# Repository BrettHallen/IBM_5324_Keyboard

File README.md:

# IBM System/23 Model 5324 Keyboard
Recreation of the keyboard for this computer to bring those without keyboards back to life.

## [Design References](/Design_Reference)

|     |Column A|Column B|Column C|Column D|Column E|Column F|Column G|Column H|Column I|Column J|Column K|
|-----|--------|--------|--------|--------|--------|--------|--------|--------|--------|--------|--------|
|Row 1| 6F/7F  | 3E     | 32     | 34     | 36     | 38     | 3A     | 3C     |        | 4B     |        |
|Row 2| 7C     | 31     | 33     | 35     | 37     |        | 39     | 3B     | 3D T   | 48     | 4C     |
|Row 3| 6D     | 20     | 22     | 24     | 26     |        | 28     | 2A     | 2C     | 47     | 49     |
|Row 4| 6C     | 54/74  | 21     | 23     | 25     | 27     | 29     | 2B     | 2D     | 44     | 4E     |
|Row 5| 6E     | 57/77  | 11     | 13     | 15     | 17     | 19     | 1B     | 59/79  | 45     | 46     |
|Row 6| 7D     | 70 T   | 12     | 14     | 16     |        | 18     | 1A     | 56/76  | 41     | 43     |
|Row 7| 71 T   | 73 T   | 0E     | 03     | 05     | 06     | 07     | 09     | 0B/7B  | 42     | 4D     |
|Row 8| 72 T   | 7E/5E  | 01     | 02     | 04     | 0F T   | 08     | 0A     | 68/78  | 40     | 4A     |

xx/yy = make/break key (send on release)<br>
T = typamatic key (repeat while held)<br>

## Keyboard Data Flow 
Refer p3-19 of the [SY34-0241-1 service manual.](/Datasheets/SY34-0241-1_IBM_5324_Computer_Service_Manual_May82_Keyboard.pdf)

The original keyboard uses a capacitive matrix where there is a capacitor for each key. When a key is pressed the capacitance increases.<br>

In my design we use standard key switches.<br>

The keyboard MCU has 11 drive lines to repeatedly scan the matrix - in my schematic these are the columns.<br>  

The increased capacitance of the active key's capacitor permits the drive-line (column) scan pulse to appear at one of the eight input lines to the sense amplifier - in my schematic these are the rows.<br>

The MCU uses the combination of the active drive line (column) and sense amplifier input line (row) to determine a scan code character (88 possible, 83 actually used).<br>

In my design the columns and rows are pulled high.  To scan the keyboard matrix we take each column low in turn.  A key press is detected when the key switch shorts the row to the column, taking the row low which is detected by the controller.  The combination of column and row is translated to a 5324 scan code and put on the bus via a buffer to ensure the 5324 accurately reads the code.<br>

An interrupt request (via DATA STROBE?) is sent to the Model 5324 processing unit which will then read the scan code character.<br>

## Key Caps
[Key cap layout](https://gist.github.com/0ddjob/6a0642893fc0fdca74740a1e6c51e858)

|Size |Count|
|-----|-----|
|1u   |68   |
|1.25u|2    |
|1.5u |2    |
|1.75u|2    |
|2u   |6    |
|2.25u|1    |
|3u   |1    |
|9.5u |1    |
|TOTAL|83   |

|Size|Key|
|-----|---|
|1.25u|Backslash|
|1.25u|Shift LH|
|1.5u|Shift RH|
|1.5u|Field Advance|
|1.75u|Backspace|
|1.75u|Shift Lock|
|2u|Field Exit|
|2u|NP +|
|2u|NP -|
|2u|NP 0|
|2u|NP .|
|2u|Alt|
|2u|Enter (vertical)|
|3u|Field + (vertical)|
|9.5u|Space|

## [KiCad Design](/KiCad)
[Schematic](/IBM_5324_Keyboard_Schematic.pdf)

## [N-Key Rollover (NKRO) Design](/KiCad_NKRO)
Adding diodes to each key switch on their row connection.  The original keyboard doesn't have these so the modified behaviour might not be expected, thus it's "experimental".

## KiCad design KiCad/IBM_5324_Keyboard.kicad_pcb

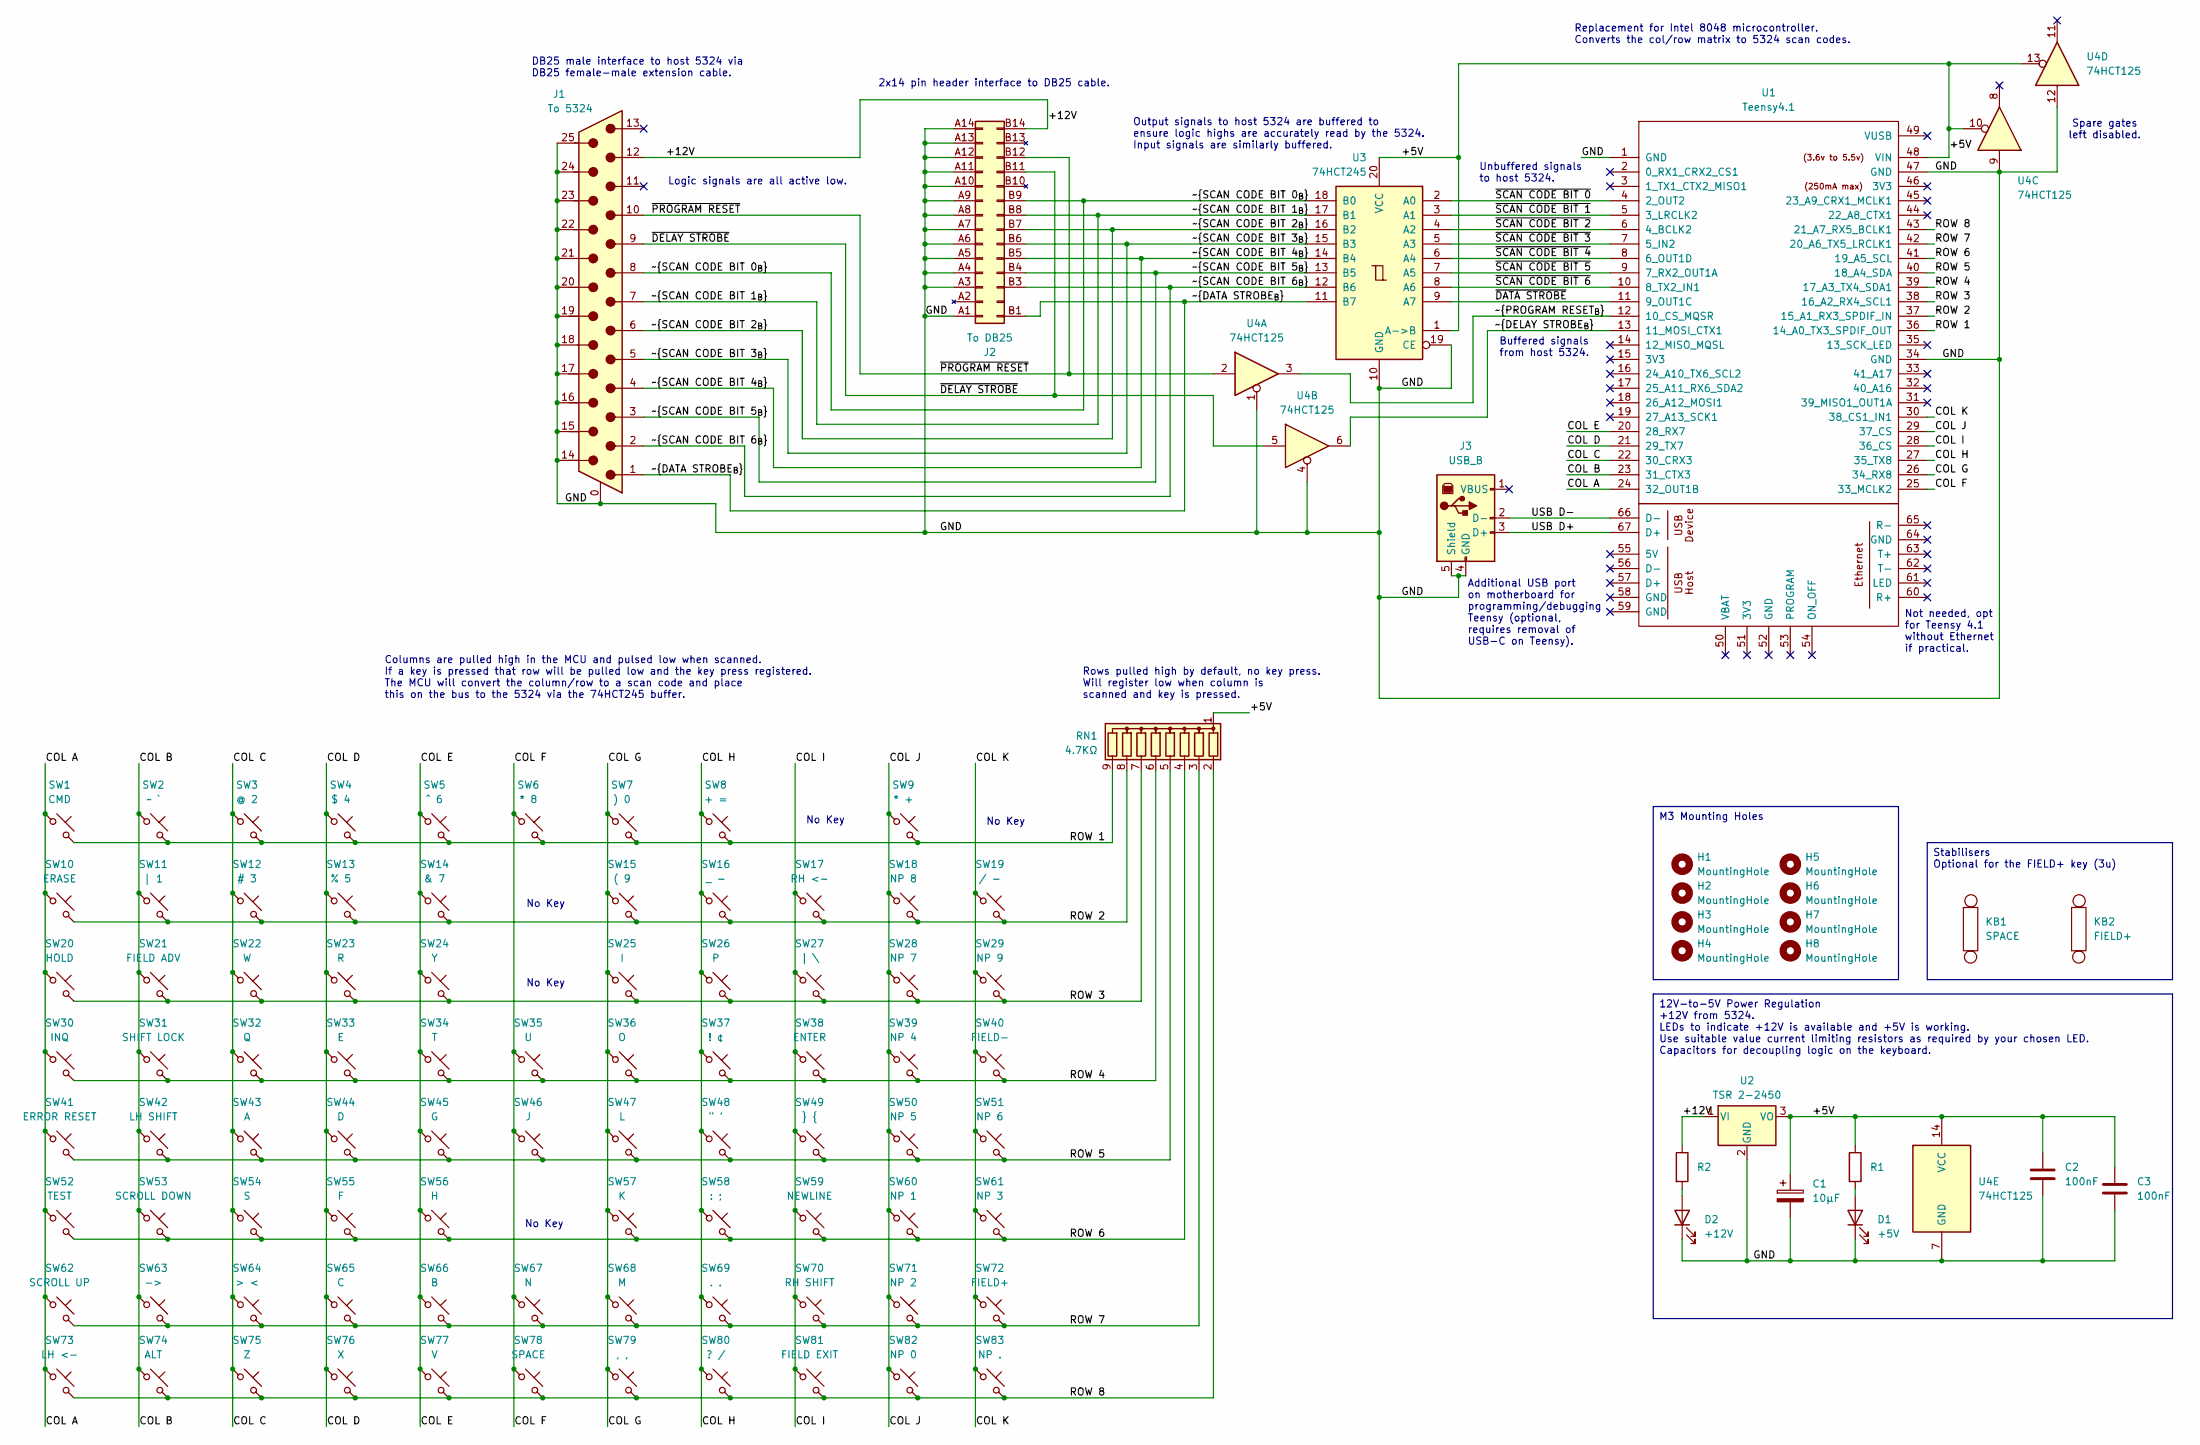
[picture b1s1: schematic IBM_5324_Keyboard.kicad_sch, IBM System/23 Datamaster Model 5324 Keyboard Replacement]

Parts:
C1: 10µF; CP_Radial_D5.0mm_P2.50mm
C2, C3: 100nF; C_Disc_D3.8mm_W2.6mm_P2.50mm
D1: +5V; LED_D5.0mm
D2: +12V; LED_D5.0mm
H1, H2, H3, H4, H5, H6, H7, H8: MountingHole; MountingHole_3.2mm_M3
J1: To 5324; L717SDB25P1ACH3R
J2: To DB25; PinHeader_2x14_P2.54mm_Vertical
J3: USB_B; USB_B_Lumberg_2411_02_Horizontal
KB1: SPACE; Stabilizer_Cherry_MX_8.00u
KB2: FIELD+; Stabilizer_Cherry_MX_3.00u
R1, R2: R; R_Axial_DIN0207_L6.3mm_D2.5mm_P7.62mm_Horizontal
RN1: 4.7KΩ; R_Array_SIP9
SW1: CMD; SW_Cherry_MX_PCB
SW2: ~ `; SW_Cherry_MX_PCB
SW3: @ 2; SW_Cherry_MX_PCB
SW4: $ 4; SW_Cherry_MX_PCB
SW5: ^ 6; SW_Cherry_MX_PCB
SW6: * 8; SW_Cherry_MX_PCB
SW7: ) 0; SW_Cherry_MX_PCB
SW8: + =; SW_Cherry_MX_PCB
SW9: * +; SW_Cherry_MX_PCB_1.75u
SW10: ERASE; SW_Cherry_MX_PCB
SW11: | 1; SW_Cherry_MX_PCB
SW12: # 3; SW_Cherry_MX_PCB
SW13: % 5; SW_Cherry_MX_PCB
SW14: & 7; SW_Cherry_MX_PCB
SW15: ( 9; SW_Cherry_MX_PCB
SW16: _ -; SW_Cherry_MX_PCB
SW17: RH <-; SW_Cherry_MX_PCB
SW18: NP 8; SW_Cherry_MX_PCB
SW19: / -; SW_Cherry_MX_PCB_1.75u
SW20: HOLD; SW_Cherry_MX_PCB
SW21: FIELD ADV; SW_Cherry_MX_PCB_1.50u
SW22: W; SW_Cherry_MX_PCB
SW23: R; SW_Cherry_MX_PCB
SW24: Y; SW_Cherry_MX_PCB
SW25: I; SW_Cherry_MX_PCB
SW26: P; SW_Cherry_MX_PCB
SW27: | \; SW_Cherry_MX_PCB
SW28: NP 7; SW_Cherry_MX_PCB
SW29: NP 9; SW_Cherry_MX_PCB
SW30: INQ; SW_Cherry_MX_PCB
SW31: SHIFT LOCK; SW_Cherry_MX_PCB_1.75u
SW32: Q; SW_Cherry_MX_PCB
SW33: E; SW_Cherry_MX_PCB
SW34: T; SW_Cherry_MX_PCB
SW35: U; SW_Cherry_MX_PCB
SW36: O; SW_Cherry_MX_PCB
SW37: ! ¢; SW_Cherry_MX_PCB
SW38: ENTER; SW_Cherry_MX_PCB_2.00u_90deg
SW39: NP 4; SW_Cherry_MX_PCB
SW40: FIELD-; SW_Cherry_MX_PCB
SW41: ERROR RESET; SW_Cherry_MX_PCB
SW42: LH SHIFT; SW_Cherry_MX_PCB_1.25u
SW43: A; SW_Cherry_MX_PCB
SW44: D; SW_Cherry_MX_PCB
SW45: G; SW_Cherry_MX_PCB
SW46: J; SW_Cherry_MX_PCB
SW47: L; SW_Cherry_MX_PCB
SW48: " '; SW_Cherry_MX_PCB
SW49: } {; SW_Cherry_MX_PCB
SW50: NP 5; SW_Cherry_MX_PCB
SW51: NP 6; SW_Cherry_MX_PCB
SW52: TEST; SW_Cherry_MX_PCB
SW53: SCROLL DOWN; SW_Cherry_MX_PCB
SW54: S; SW_Cherry_MX_PCB
SW55: F; SW_Cherry_MX_PCB
SW56: H; SW_Cherry_MX_PCB
SW57: K; SW_Cherry_MX_PCB
SW58: : ;; SW_Cherry_MX_PCB
SW59: NEWLINE; SW_Cherry_MX_PCB
SW60: NP 1; SW_Cherry_MX_PCB
SW61: NP 3; SW_Cherry_MX_PCB
SW62: SCROLL UP; SW_Cherry_MX_PCB
SW63: ->; SW_Cherry_MX_PCB
SW64: > <; SW_Cherry_MX_PCB_1.00u
SW65: C; SW_Cherry_MX_PCB
SW66: B; SW_Cherry_MX_PCB
SW67: N; SW_Cherry_MX_PCB
SW68: M; SW_Cherry_MX_PCB
SW69: . .; SW_Cherry_MX_PCB
SW70: RH SHIFT; SW_Cherry_MX_PCB_1.50u
SW71: NP 2; SW_Cherry_MX_PCB
SW72: FIELD+; SW_Cherry_MX_PCB_3.00u_90deg
SW73: LH <-; SW_Cherry_MX_PCB
SW74: ALT; SW_Cherry_MX_PCB_2.25u
SW75: Z; SW_Cherry_MX_PCB
SW76: X; SW_Cherry_MX_PCB
SW77: V; SW_Cherry_MX_PCB
SW78: SPACE; SW_Cherry_MX_PCB
SW79: , ,; SW_Cherry_MX_PCB
SW80: ? /; SW_Cherry_MX_PCB
SW81: FIELD EXIT; SW_Cherry_MX_PCB_2.00u
SW82: NP 0; SW_Cherry_MX_PCB_2.00u
SW83: NP .; SW_Cherry_MX_PCB_2.00u
U1: Teensy4.1; Teensy41
U2: TSR 2-2450; Converter_DCDC_TRACO_TSR2-24xxN_TSR2-24xxxN_THT
U3: 74HCT245; DIP-20_W7.62mm
U4: 74HCT125; DIP-14_W7.62mm

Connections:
/+5V: C1.1, C2.1, C3.1, R1.1, RN1.1 (common), U1.48 (VIN), U2.3 (VO), U3.1 (A->B), U3.20 (VCC), U4.10, U4.13, U4.14 (VCC)
/+12V: J1.12, J2.B14 (+12V), R2.1, U2.1 (VI)
/GND: C1.2, C2.2, C3.2, D1.1 (K), D2.1 (K), J1.0 (PAD), J1.14, J1.15, J1.16, J1.17, J1.18, J1.19, J1.20, J1.21, J1.22, J1.23, J1.24, J1.25, J2.A1 (GND), J2.A3 (GND), J2.A4 (GND), J2.A5 (GND), J2.A6 (GND), J2.A7 (GND), J2.A8 (GND), J2.A9 (GND), J2.A10 (GND), J2.A11 (GND), J2.A12 (GND), J2.A13 (GND), J2.A14 (GND), J3.4 (GND), J3.5 (Shield), U1.1 (GND), U1.34 (GND), U1.47 (GND), U2.2 (GND), U3.10 (GND), U3.19 (CE), U4.1, U4.4, U4.7 (GND), U4.9, U4.12
/USB D+: J3.3 (D+), U1.67 (D+)
/USB D-: J3.2 (D-), U1.66 (D-)
/~DATA STROBE_{B}: J1.1, J2.B1 (DATA_STROBE), U3.11 (B7)
/~DATA STROBE: U1.11 (9_OUT1C), U3.9 (A7)
/~DELAY STROBE_{B}: U1.13 (11_MOSI_CTX1), U4.6
/~DELAY STROBE: J1.9, J2.B11 (DELAY_STROBE), U4.5
/~PROGRAM RESET_{B}: U1.12 (10_CS_MQSR), U4.3
/~PROGRAM RESET: J1.10, J2.B12 (PROGRAM_RESET), U4.2
/~SCAN CODE BIT 0_{B}: J1.8, J2.B9 (SCAN_CODE_BIT_0), U3.18 (B0)
/~SCAN CODE BIT 0: U1.4 (2_OUT2), U3.2 (A0)
/~SCAN CODE BIT 1_{B}: J1.7, J2.B8 (SCAN_CODE_BIT_1), U3.17 (B1)
/~SCAN CODE BIT 1: U1.5 (3_LRCLK2), U3.3 (A1)
/~SCAN CODE BIT 2_{B}: J1.6, J2.B7 (SCAN_CODE_BIT_2), U3.16 (B2)
/~SCAN CODE BIT 2: U1.6 (4_BCLK2), U3.4 (A2)
/~SCAN CODE BIT 3_{B}: J1.5, J2.B6 (SCAN_CODE_BIT_3), U3.15 (B3)
/~SCAN CODE BIT 3: U1.7 (5_IN2), U3.5 (A3)
/~SCAN CODE BIT 4_{B}: J1.4, J2.B5 (SCAN_CODE_BIT_4), U3.14 (B4)
/~SCAN CODE BIT 4: U1.8 (6_OUT1D), U3.6 (A4)
/~SCAN CODE BIT 5_{B}: J1.3, J2.B4 (SCAN_CODE_BIT_5), U3.13 (B5)
/~SCAN CODE BIT 5: U1.9 (7_RX2_OUT1A), U3.7 (A5)
/~SCAN CODE BIT 6_{B}: J1.2, J2.B3 (SCAN_CODE_BIT_6), U3.12 (B6)
/~SCAN CODE BIT 6: U1.10 (8_TX2_IN1), U3.8 (A6)
Col_A: SW1.1, SW10.1, SW20.1, SW30.1, SW41.1, SW52.1, SW62.1, SW73.1, U1.24 (32_OUT1B)
Col_B: SW2.1, SW11.1, SW21.1, SW31.1, SW42.1, SW53.1, SW63.1, SW74.1, U1.23 (31_CTX3)
Col_C: SW3.1, SW12.1, SW22.1, SW32.1, SW43.1, SW54.1, SW64.1, SW75.1, U1.22 (30_CRX3)
Col_D: SW4.1, SW13.1, SW23.1, SW33.1, SW44.1, SW55.1, SW65.1, SW76.1, U1.21 (29_TX7)
Col_E: SW5.1, SW14.1, SW24.1, SW34.1, SW45.1, SW56.1, SW66.1, SW77.1, U1.20 (28_RX7)
Col_F: SW6.1, SW35.1, SW46.1, SW67.1, SW78.1, U1.25 (33_MCLK2)
Col_G: SW7.1, SW15.1, SW25.1, SW36.1, SW47.1, SW57.1, SW68.1, SW79.1, U1.26 (34_RX8)
Col_H: SW8.1, SW16.1, SW26.1, SW37.1, SW48.1, SW58.1, SW69.1, SW80.1, U1.27 (35_TX8)
Col_I: SW17.1, SW27.1, SW38.1, SW49.1, SW59.1, SW70.1, SW81.1, U1.28 (36_CS)
Col_J: SW9.1, SW18.1, SW28.1, SW39.1, SW50.1, SW60.1, SW71.1, SW82.1, U1.29 (37_CS)
Col_K: SW19.1, SW29.1, SW40.1, SW51.1, SW61.1, SW72.1, SW83.1, U1.30 (38_CS1_IN1)
unnamed: D1.2 (A), R1.2
unnamed: D2.2 (A), R2.2
Row_1: RN1.9 (R8), SW1.2, SW2.2, SW3.2, SW4.2, SW5.2, SW6.2, SW7.2, SW8.2, SW9.2, U1.36 (14_A0_TX3_SPDIF_OUT)
Row_2: RN1.8 (R7), SW10.2, SW11.2, SW12.2, SW13.2, SW14.2, SW15.2, SW16.2, SW17.2, SW18.2, SW19.2, U1.37 (15_A1_RX3_SPDIF_IN)
Row_3: RN1.7 (R6), SW20.2, SW21.2, SW22.2, SW23.2, SW24.2, SW25.2, SW26.2, SW27.2, SW28.2, SW29.2, U1.38 (16_A2_RX4_SCL1)
Row_4: RN1.6 (R5), SW30.2, SW31.2, SW32.2, SW33.2, SW34.2, SW35.2, SW36.2, SW37.2, SW38.2, SW39.2, SW40.2, U1.39 (17_A3_TX4_SDA1)
Row_5: RN1.5 (R4), SW41.2, SW42.2, SW43.2, SW44.2, SW45.2, SW46.2, SW47.2, SW48.2, SW49.2, SW50.2, SW51.2, U1.40 (18_A4_SDA)
Row_6: RN1.4 (R3), SW52.2, SW53.2, SW54.2, SW55.2, SW56.2, SW57.2, SW58.2, SW59.2, SW60.2, SW61.2, U1.41 (19_A5_SCL)
Row_7: RN1.3 (R2), SW62.2, SW63.2, SW64.2, SW65.2, SW66.2, SW67.2, SW68.2, SW69.2, SW70.2, SW71.2, SW72.2, U1.42 (20_A6_TX5_LRCLK1)
Row_8: RN1.2 (R1), SW73.2, SW74.2, SW75.2, SW76.2, SW77.2, SW78.2, SW79.2, SW80.2, SW81.2, SW82.2, SW83.2, U1.43 (21_A7_RX5_BCLK1)

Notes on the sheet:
Columns are pulled high in the MCU and pulsed low when scanned. If a key is pressed that row will be pulled low and the key press registered. The MCU will convert the column/row to a scan code and place this on the bus to the 5324 via the 74HCT245 buffer.
Buffered signals from host 5324.
No Key
Additional USB port on motherboard for programming/debugging Teensy (optional, requires removal of USB-C on Teensy).
Spare gates left disabled.
Logic signals are all active low.
2x14 pin header interface to DB25 cable.
Replacement for Intel 8048 microcontroller. Converts the col/row matrix to 5324 scan codes.
DB25 male interface to host 5324 via DB25 female-male extension cable.
Unbuffered signals to host 5324.
Output signals to host 5324 are buffered to ensure logic highs are accurately read by the 5324. Input signals are similarly buffered.
Rows pulled high by default, no key press. Will register low when column is scanned and key is pressed.
Not needed, opt for Teensy 4.1 without Ethernet if practical.
M3 Mounting Holes
Stabilisers Optional for the FIELD+ key (3u)
12V-to-5V Power Regulation +12V from 5324. LEDs to indicate +12V is available and +5V is working. Use suitable value current limiting resistors as required by your chosen LED. Capacitors for decoupling logic on the keyboard.

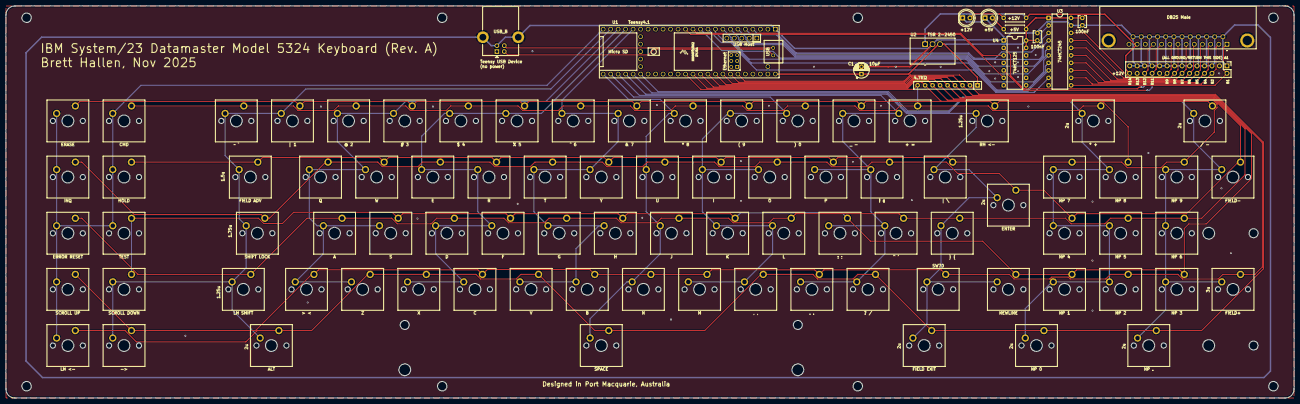
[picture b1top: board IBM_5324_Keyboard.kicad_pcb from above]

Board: 2 copper layers, 437.0 x 133.0 mm, 108 parts (0 on the bottom side), 46 nets.

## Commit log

2025-11-26 Finalise keyboard matrix layout
2025-11-26 Keycap layout design
2025-11-26 PCB layout started
2025-11-27 Added keyboard-specific section
2025-11-27 Keyboard Data Flow
2025-11-27 Added scan codes
2025-11-27 Initial layout completed
2025-11-27 Fixed file naming
2025-11-28 Generate Gerbers for testing, maybe
2025-11-29 Added 74LS125 buffer for incoming signals
2025-11-30 Annotated disassembly of the keyboard controller
2025-11-30 Added USB-B socket for Teensy programming/debugging
2025-12-02 Reduced ground plane clearance to 0.3mm
